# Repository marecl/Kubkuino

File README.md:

# Contactless liquid watchdog

Perfect for watching your coffee. Now you won't forget, that you've made one.

Directories:  
	* Dokumentacje - Documentation and final version of PC software  
	* Kubkuino - source code and case drawings  
	* Kubkuino_PC - PC software sources  
	* Obsolete - Old version  
	* RawDoc - Raw data for documentation  

ToDo list:  
	-Notification bar alarm,  
	-Print all COM ports on startup,   
	-Manual,  
	-Automatic config creation,
	-Migrate to V-USB?
  
Navigation:  
	1 click - enter menu/next item  
	Press and hold - Select/switch  
	
Arduino:  
  
	Source:  
		#define _NAME (String)"[NAME]" - Device default name  
		#define _PASS (String)"[4 digits]" - Set Bluetooth pairing PIN code  
		#define TONE [freq/tone] - Alarm frequency (or tone, based on vars.h)  
		#define ALARM_TIME [milliseconds] - Alarm duration  
  
	Bluetooth commands:  
		e; - Establish a connection (returns "HELLO\r\n") - must be sent!  
		qquit; - Disconnect - must be sent! 
		CXX.X; - Set 'cold' temperature  
		HXX.X; - Set 'hot' temperature  
		C?;/H?; - Check temperatures  
		r; - Current reading  
		S[AT command]; - Executes arbitary AT command, returns module's response  
		DXY; - Management:  
			0Y* - LCD  
			1Y* - Backlight  
			2Y* - Bluetooth  
			3Y* - LED  
			4Y* - Alarm mute  
			5 - Status of: LCD, Backlight, LED, Mute (4 bits)
			6 - Sleep mode  
			B - Revert bluetooth module to factory defaults  
			D - Device defaults  
			L - Load settings from EEPROM  
			S - Save settings to EEPROM  
  
		*(0 - OFF, 1 - ON, ? - Check status)

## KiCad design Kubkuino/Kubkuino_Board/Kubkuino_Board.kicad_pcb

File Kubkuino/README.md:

Parts:
* SSD1306 128x64 OLED display
* 3 LEDs - red, green and blue
* MLX90614 IR temperature sensor

Designed in KiCAD.  
Board has two layers, but the bottom one is only for ICSP header.  
All goldpin headers/sockets are SMD.

Drawings made in DraftSight. Unfortunately - you have to measure everything on your own.

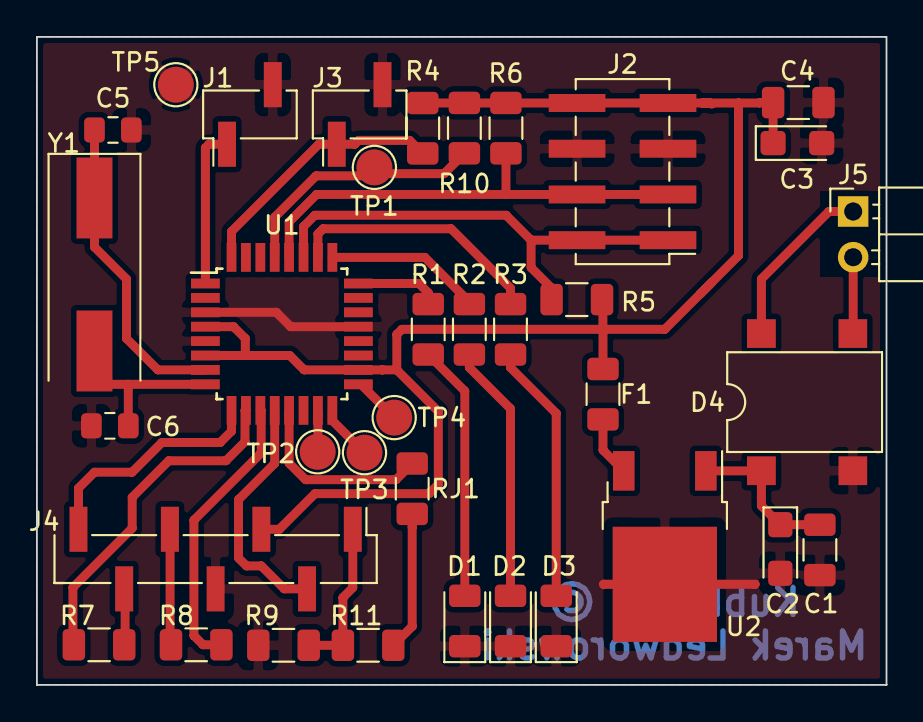
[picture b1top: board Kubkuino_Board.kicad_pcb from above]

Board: 2 copper layers, 47.2 x 36.0 mm, 36 parts (0 on the bottom side), 31 nets.

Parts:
C1, C4: 100nF; C_1206_3216Metric
C2, C3: 1uF; CP_EIA-3216-18_Kemet-A
C5, C6: 22pF; C_0805_2012Metric_Pad1.15x1.40mm_HandSolder
D1: LED_R; LED_1206_3216Metric
D2: LED_G; LED_1206_3216Metric
D3: LED_B; LED_1206_3216Metric
D4: DF08M; Diode_Bridge_DIP-4_W7.62mm_P5.08mm
F1: 500mA 6V; R_1206_3216Metric
J1: Piezo; PinHeader_1x02_P2.54mm_Vertical_SMD_Pin1Left
J2: I2C; PinHeader_2x04_P2.54mm_Vertical_SMD
J3: Button; PinHeader_1x02_P2.54mm_Vertical_SMD_Pin1Left
J4: Bluetooth; PinHeader_1x07_P2.54mm_Vertical_SMD_Pin1Left
J5: AC/DC In (12V); PinHeader_1x02_P2.54mm_Horizontal
R1, R2, R3: 220; R_1206_3216Metric
R4: 1k; R_1206_3216Metric
R5, R6, R7, R8, R11: 4k7; R_1206_3216Metric
R9, R10: 10k; R_1206_3216Metric
RJ1: 0; R_1206_3216Metric
TP1: RESET; TestPoint_Pad_D2.0mm
TP2: MOSI; TestPoint_Pad_D2.0mm
TP3: MISO; TestPoint_Pad_D2.0mm
TP4: SCK; TestPoint_Pad_D2.0mm
TP5: GND; TestPoint_Pad_D2.0mm
U1: ATmega328P-AU; TQFP-32_7x7mm_P0.8mm
U2: LM7805_TO220; TO-252-2
Y1: Crystal; Crystal_SMD_HC49-SD

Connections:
5V: C3.1, C4.1, F1.1, J2.7, J2.8, J4.3, R4.1, R5.2, R6.2, R10.1, U1.4, U1.6, U1.18
/MISO: TP3.1, U1.16
/MOSI: TP2.1, U1.15
/SCK: TP4.1, U1.17
BTen: J4.2, U1.12
BTkey: RJ1.1, U1.13
Brx: R7.2, U1.10
BtConn: J4.7, U1.9
Btx: R8.2, U1.11
Button: J3.1, R4.2, U1.32
GND: C1.2, C2.2, C3.2, C4.2, C5.2, C6.2, D1.1, D2.1, D3.1, D4.2, J1.2, J2.5, J2.6, J3.2, J4.4, R9.1, TP5.1, U1.3, U1.5, U1.21, U2.2
unnamed: C1.1, C2.1, D4.1, U2.1
unnamed: D1.2, R1.1
unnamed: D2.2, R2.1
unnamed: D3.2, R3.1
unnamed: D4.3, J5.2
unnamed: D4.4, J5.1
unnamed: F1.2, U2.3
unnamed: J1.1, U1.1
unnamed: J4.1, R9.2, R11.2
unnamed: J4.5, R8.1
unnamed: J4.6, R7.1
unnamed: R1.2, U1.24
unnamed: R2.2, U1.25
unnamed: R3.2, U1.26
unnamed: R11.1, RJ1.2
Reset: R10.2, TP1.1, U1.29
SCL: J2.3, J2.4, R6.1, U1.28
SDA: J2.1, J2.2, R5.1, U1.27
xtal1: C5.1, U1.7, Y1.1
xtal2: C6.1, U1.8, Y1.2

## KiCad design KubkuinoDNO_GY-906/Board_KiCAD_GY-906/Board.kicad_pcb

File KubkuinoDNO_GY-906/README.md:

# Specjalizowany czujnik temperaturowy:
## Mikroprocesorowy analizator cieplny

Zrobiłeś kawę albo herbatę i nie chcesz pilnować aż ostygnie? To coś dla Ciebie!
  
Do zrobienia:  
	-Ładniejszy interfejs,  
	-Naprawa wskaźników temperatury  
	-Rozróżnianie HELLO_STD od HELLO_IR (GY-906)  
	-Zmiana wyświetlacza na SSD1306 128x32 (i2c)  
	
Arduino:  
  
	Kod:  
		#define _NAME (String)"[NAZWA]" - Ustawia nazwę jako domyślną  
		#define _PASS (String)"[4 cyfry]" - Ustawia wpisane cyfry jako hasło do parowania  
		#define TONE [TON] - Dźwięk alarmu (uzupełnić na podstawie vars.h)  
		#define ALARM_TIME [milisekundy] - Ile milisekund Arduino ma piszczeć  
  
	Komendy:  
		X - Pierwszy argument  
		Y - Drugi argument  
  
		e; - Nawiązanie połączenia (zwraca "HELLO_IR\r\n") MUSI ZOSTAĆ WYSŁANE  
		qquit; - Rozłączenie MUSI ZOSTAĆ WYSŁANE (specjanie takie długie - na wypadek błędu komunikacji,  
			który wysyła 'q' zamiast 'r'. Nie wiem czemu.)  
		CXX.X; - Ustawienie temperatury zimna  
		HXX.X; - Ustawienie temperatury ciepła  
			C?;/H?; - sprawdzenie temperatur  
		S[komenda AT]; - Przesyła komendę AT do modułu Bluetooth. Zwraca odpowiedź modułu.  
		d; - Reset modułu Bluetooth, ustawienie domyślnej nazwy i hasła  
		r - Zwraca bieżący odczyt z czujnika  
		t; - Zwraca stan jako char (H - Hot, R - Ready, C - Cold)  
		DXY; - Moduł zarządzania komponentami:  
			0Y* - LCD (1 - włącz, 0 - wyłącz)  
			1Y* - Podswietlenie (1 - włącz, 0 - wyłącz)  
			2Y - BT (1 - włącz, 0 - wyłącz)  
			3Y* - LED (1 - włącz, 0 - wyłącz)  
			4Y* - Wyciszenie (1 - wyciszony, 0 - głośny)  
			6 - Status LCD, Podświetlenie, LED, Alarm (1 - włączony, 0 - wyłączony)  
			8 - Przejście w tryb uśpienia  
  
		*Jak jako argument poda się znak zapytania (?) zostanie zwrócony stan pojedynczego modułu  
  
Każda komenda jest zakończona średnikiem ';'!

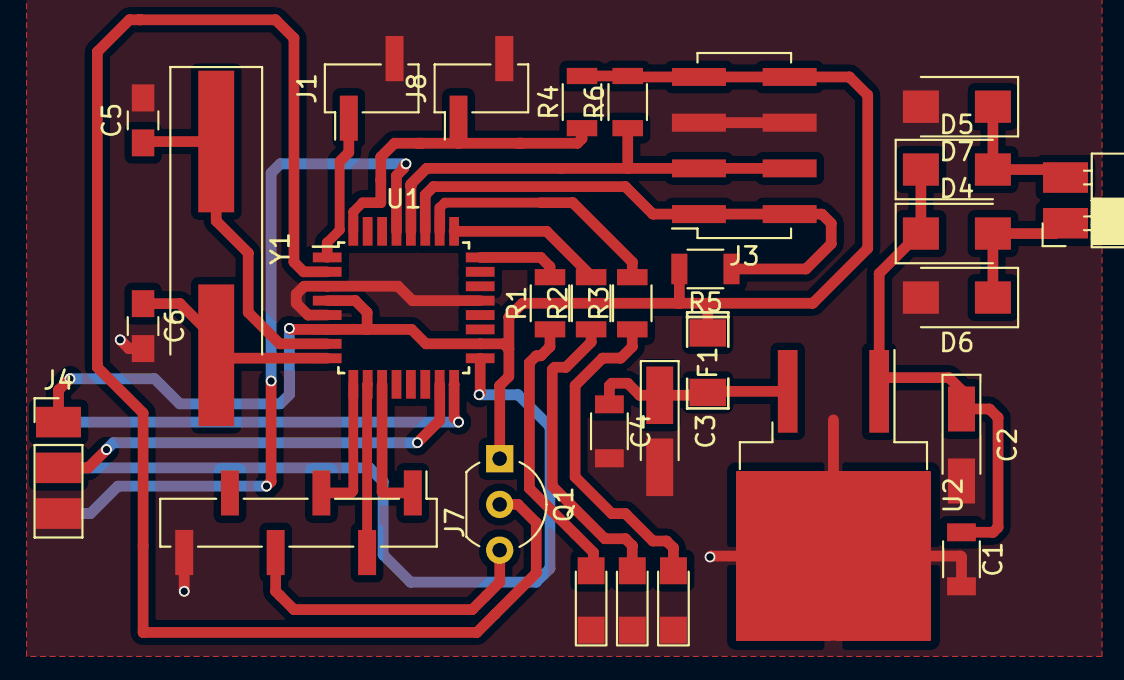
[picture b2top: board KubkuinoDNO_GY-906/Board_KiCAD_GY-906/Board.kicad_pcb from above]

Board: 2 copper layers, 31 parts (1 on the bottom side), 27 nets.

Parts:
C1, C4: 100nF; C_1206
C2, C3: 1uF; CP_Tantalum_Case-A_EIA-3216-18_Hand
C5, C6: 22pF; C_0805_HandSoldering
D1: LED_R; LED_1206
D2: LED_G; LED_1206
D3: LED_B; LED_1206
D4, D5, D6, D7: 1N4007; D_SMA
F1: 500mA 6V; SMD-1206_Pol
J1: Piezo; Pin_Header_Straight_1x02_Pitch2.54mm_SMD_Pin1Left
J2, J4: Conn_01x03; Socket_Strip_Straight_1x03_Pitch2.54mm
J3: I2C; Socket_Strip_Straight_2x04_Pitch2.54mm_SMD
J6: AC/DC In (12V); Socket_Strip_Angled_1x02_Pitch2.54mm
J7: Bluetooth; Pin_Header_Straight_1x06_Pitch2.54mm_SMD_Pin1Left
J8: Button; Pin_Header_Straight_1x02_Pitch2.54mm_SMD_Pin1Left
Q1: S8050; TO-92_Inline_Wide
R1, R2, R3: 220; R_1206
R4: 1k; R_1206
R5, R6: 4k7; R_1206
U1: ATMEGA328P-AU; TQFP-32_7x7mm_Pitch0.8mm
U2: LM7805_TO220; TO-263-2
Y1: Crystal; Crystal_SMD_HC49-SD_HandSoldering

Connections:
5V: F1.1, J3.7, J3.8, J4.1, Q1.1, R4.2, R5.2, R6.2, U1.4, U1.6, U1.18
BT: Q1.2, U1.2
Bkey: J7.1, U1.11
Brx: J7.2, U1.10
Btx: J7.3, U1.9
Button: J8.1, R4.1, U1.32
GND: C1.2, C2.2, C3.2, C4.2, C5.2, C6.2, D1.1, D2.1, D3.1, D6.2, D7.2, J1.2, J3.5, J3.6, J4.3, J7.6, J8.2, U1.3, U1.5, U1.21, U2.2
unnamed: C1.1, C2.1, D4.1, D5.1, U2.1
unnamed: C3.1, C4.1, F1.2, U2.3
unnamed: D1.2, R1.1
unnamed: D2.2, R2.1
unnamed: D3.2, R3.1
unnamed: D4.2, D6.1, J6.1
unnamed: D5.2, D7.1, J6.2
unnamed: J1.1, U1.1
unnamed: J2.1, U1.16
unnamed: J2.2, U1.17
unnamed: J4.2, U1.15
unnamed: J7.4, Q1.3
unnamed: R1.2, U1.24
unnamed: R2.2, U1.25
unnamed: R3.2, U1.26
Reset: J2.3, U1.29
SCL: J3.3, J3.4, R6.1, U1.28
SDA: J3.1, J3.2, R5.1, U1.27
xtal1: C5.1, U1.7, Y1.1
xtal2: C6.1, U1.8, Y1.2

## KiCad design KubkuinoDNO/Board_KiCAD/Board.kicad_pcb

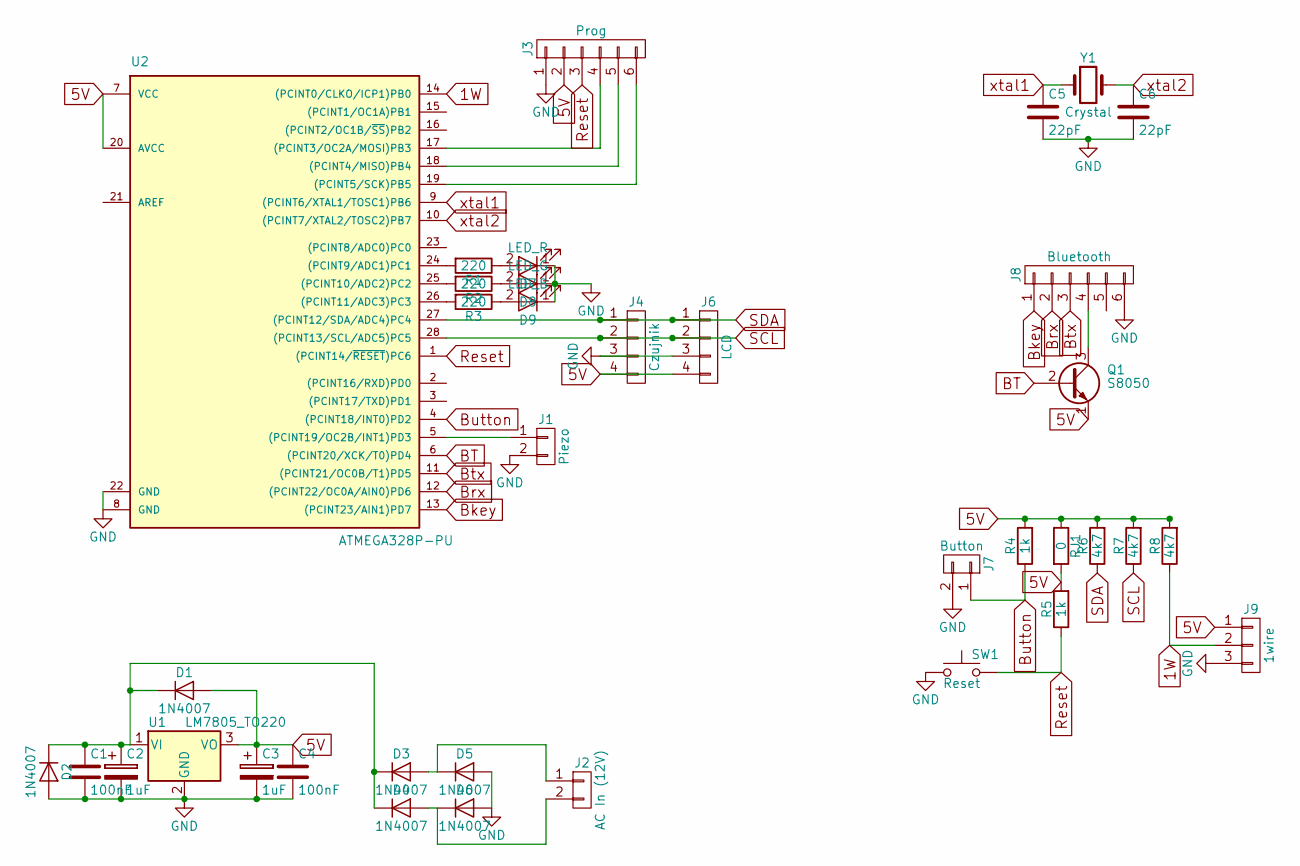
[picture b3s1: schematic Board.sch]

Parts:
C1, C4: 100nF; C_1206
C2, C3: 1uF; CP_Tantalum_Case-A_EIA-3216-18_Hand
C5, C6: 22pF; C_0805_HandSoldering
D1, D2, D3, D4, D5, D6: 1N4007; D_SMA
D7: LED_R; LED_1206
D8: LED_G; LED_1206
D9: LED_B; LED_1206
J1: Piezo; Pin_Header_Straight_1x02_Pitch2.54mm_SMD_Pin1Left
J2: AC In (12V); Pin_Header_Straight_1x02_Pitch2.54mm_SMD_Pin1Left
J3: Prog; Pin_Header_Straight_1x06_Pitch2.54mm_SMD_Pin1Left
J4: Czujnik; Pin_Header_Straight_1x04_Pitch2.54mm_SMD_Pin1Left
J6: LCD; Pin_Header_Straight_1x04_Pitch2.54mm_SMD_Pin1Left
J7: Button; Pin_Header_Straight_1x02_Pitch2.54mm_SMD_Pin1Left
J8: Bluetooth; Pin_Header_Straight_1x06_Pitch2.54mm_SMD_Pin1Left
J9: 1wire; Pin_Header_Straight_1x03_Pitch2.54mm_SMD_Pin1Left
Q1: S8050; TO-92_Inline_Wide
R1, R2, R3: 220; R_1206
R4, R5: 1k; R_1206
R6, R7, R8: 4k7; R_1206
RJ1: 0
SW1: Reset; SW_SPST_B3SL-1002P
U1: LM7805_TO220; TO-263-2
U2: ATMEGA328P-PU; TQFP-32_7x7mm_Pitch0.8mm
Y1: Crystal; Crystal_SMD_HC49-SD

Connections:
1W: J9.2, R8.1, U2.14 ((PCINT0/CLKO/ICP1)PB0)
5V: C3.1, C4.1, D1.2 (A), J3.2, J4.4, J6.4, J9.1, Q1.1 (E), R4.2, R5.2, R6.2, R7.2, R8.2, RJ1.1, RJ1.2, U1.3 (VO), U2.7 (VCC), U2.20 (AVCC)
BT: Q1.2 (B), U2.6 ((PCINT20/XCK/T0)PD4)
Bkey: J8.1, U2.13 ((PCINT23/AIN1)PD7)
Brx: J8.2, U2.12 ((PCINT22/OC0A/AIN0)PD6)
Btx: J8.3, U2.11 ((PCINT21/OC0B/T1)PD5)
Button: J7.1, R4.1, U2.4 ((PCINT18/INT0)PD2)
GND: C1.2, C2.2, C3.2, C4.2, C5.2, C6.2, D2.2 (A), D5.2 (A), D6.2 (A), D7.1 (K), D8.1 (K), D9.1 (K), J1.2, J3.1, J4.3, J6.3, J7.2, J8.6, J9.3, SW1.1, U1.2 (GND), U2.8 (GND), U2.22 (GND)
unnamed: C1.1, C2.1, D1.1 (K), D2.1 (K), D3.1 (K), D4.1 (K), U1.1 (VI)
unnamed: D3.2 (A), D5.1 (K), J2.1
unnamed: D4.2 (A), D6.1 (K), J2.2
unnamed: D7.2 (A), R1.1
unnamed: D8.2 (A), R2.1
unnamed: D9.2 (A), R3.1
unnamed: J1.1, U2.5 ((PCINT19/OC2B/INT1)PD3)
unnamed: J3.4, U2.17 ((PCINT3/OC2A/MOSI)PB3)
unnamed: J3.5, U2.18 ((PCINT4/MISO)PB4)
unnamed: J3.6, U2.19 ((PCINT5/SCK)PB5)
unnamed: J8.4, Q1.3 (C)
unnamed: R1.2, U2.24 ((PCINT9/ADC1)PC1)
unnamed: R2.2, U2.25 ((PCINT10/ADC2)PC2)
unnamed: R3.2, U2.26 ((PCINT11/ADC3)PC3)
Reset: J3.3, R5.1, SW1.2, U2.1 ((PCINT14/~RESET~)PC6)
SCL: J4.2, J6.2, R7.1, U2.28 ((PCINT13/SCL/ADC5)PC5)
SDA: J4.1, J6.1, R6.1, U2.27 ((PCINT12/SDA/ADC4)PC4)
xtal1: C5.1, U2.9 ((PCINT6/XTAL1/TOSC1)PB6), Y1.1
xtal2: C6.1, U2.10 ((PCINT7/XTAL2/TOSC2)PB7), Y1.2

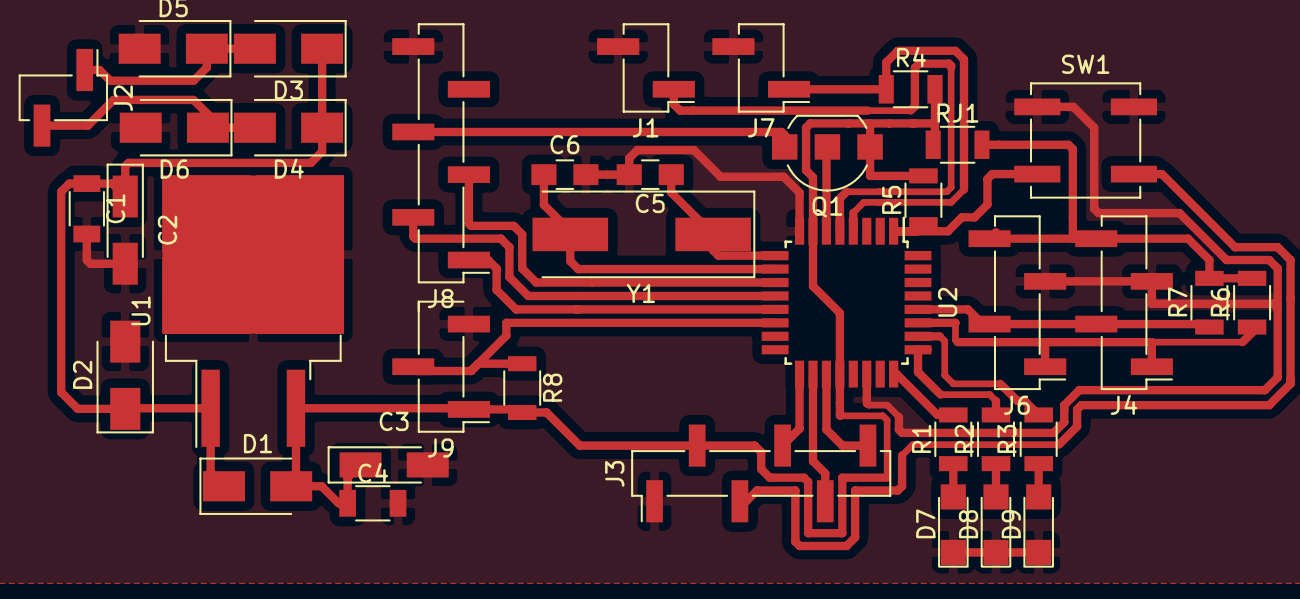
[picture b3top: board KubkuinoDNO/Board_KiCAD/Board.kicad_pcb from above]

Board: 2 copper layers, 37 parts (0 on the bottom side), 27 nets.

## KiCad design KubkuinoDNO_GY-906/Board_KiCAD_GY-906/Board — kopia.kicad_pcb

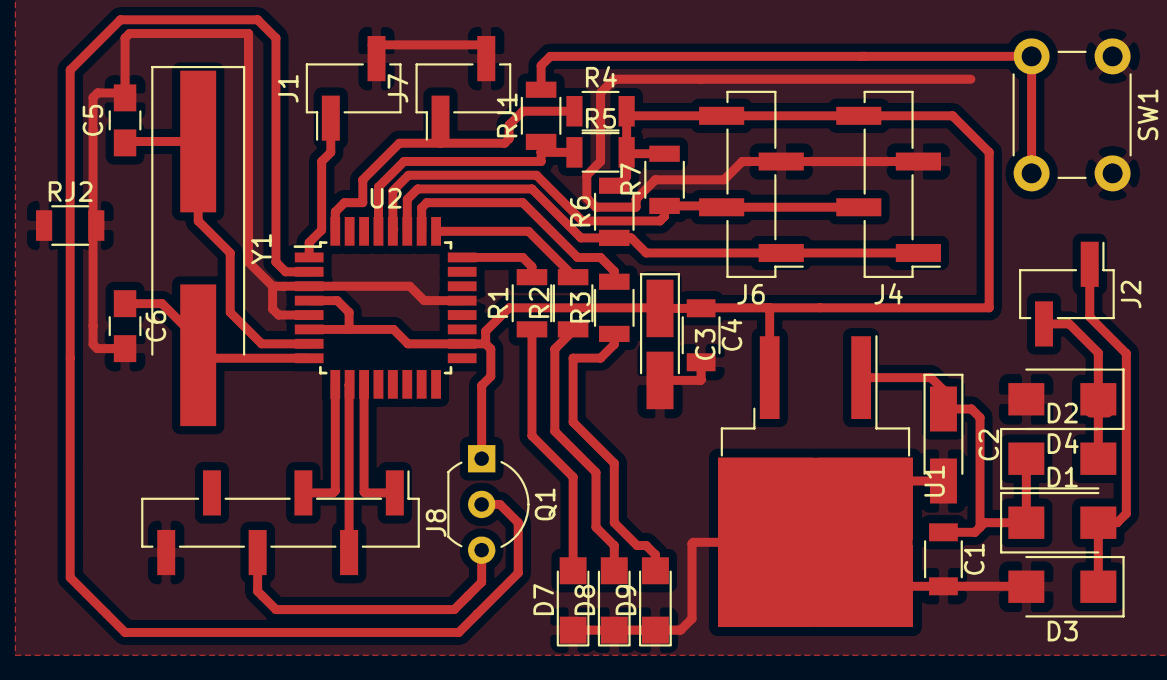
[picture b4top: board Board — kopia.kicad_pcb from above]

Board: 2 copper layers, 33 parts (0 on the bottom side), 24 nets.

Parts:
C1, C4: 100nF; C_1206
C2, C3: 1uF; CP_Tantalum_Case-A_EIA-3216-18_Hand
C5, C6: 22pF; C_0805_HandSoldering
D1, D2, D3, D4: 1N4007; D_SMA
D7: LED_R; LED_1206
D8: LED_G; LED_1206
D9: LED_B; LED_1206
J1: Piezo; Pin_Header_Straight_1x02_Pitch2.54mm_SMD_Pin1Left
J2: AC/DC In (12V); Pin_Header_Straight_1x02_Pitch2.54mm_SMD_Pin1Left
J4: Czujnik; Pin_Header_Straight_1x04_Pitch2.54mm_SMD_Pin1Left
J6: LCD; Pin_Header_Straight_1x04_Pitch2.54mm_SMD_Pin1Left
J7: Button; Pin_Header_Straight_1x02_Pitch2.54mm_SMD_Pin1Left
J8: Bluetooth; Pin_Header_Straight_1x06_Pitch2.54mm_SMD_Pin1Left
Q1: S8050; TO-92_Inline_Wide
R1, R2, R3: 220; R_1206
R4, R5: 1k; R_1206
R6, R7: 4k7; R_1206
RJ1, RJ2: 0; R_1206
SW1: Reset; SW_PUSH_6mm_h5mm
U1: LM7805_TO220; TO-263-2
U2: ATMEGA328P-AU; TQFP-32_7x7mm_Pitch0.8mm
Y1: Crystal; Crystal_SMD_HC49-SD_HandSoldering

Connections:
5V: C3.1, C4.1, J4.4, J6.4, Q1.1, R4.2, R5.2, R6.2, R7.2, U1.3, U2.4, U2.6, U2.18
BT: Q1.2, U2.2
Bkey: J8.1, U2.11
Brx: J8.2, U2.10
Btx: J8.3, U2.9
Button: J7.1, R4.1, U2.32
GND: C1.2, C2.2, C3.2, C4.2, C5.2, C6.2, D3.2, D4.2, D7.1, D8.1, D9.1, J1.2, J4.3, J6.3, J7.2, J8.6, RJ2.1, RJ2.2, SW1.1, U1.2, U2.3, U2.5, U2.21
unnamed: C1.1, C2.1, D1.1, D2.1, U1.1
unnamed: D1.2, D3.1, J2.1
unnamed: D2.2, D4.1, J2.2
unnamed: D7.2, R1.1
unnamed: D8.2, R2.1
unnamed: D9.2, R3.1
unnamed: J1.1, U2.1
unnamed: J8.4, Q1.3
unnamed: R1.2, U2.24
unnamed: R2.2, U2.25
unnamed: R3.2, U2.26
unnamed: RJ1.2, SW1.2
Reset: R5.1, RJ1.1, U2.29
SCL: J4.2, J6.2, R7.1, U2.28
SDA: J4.1, J6.1, R6.1, U2.27
xtal1: C5.1, U2.7, Y1.1
xtal2: C6.1, U2.8, Y1.2

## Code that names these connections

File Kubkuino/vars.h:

#define ctl 2 //Przycisk
#define buzz 3 //Buzzer
#define btconn 5 //BT connected
#define brx 6 //Bluetooth RX
#define btx 7 //Bluetooth TX
#define btpow 8 //Zasilanie BT
#define btkey 9 //BT Key
#define rled A1
#define gled A2
#define bled A3
#if F_CPU != 16000000
#undef F_CPU
#define F_CPU 16000000
#endif
#if (SSD1306_LCDHEIGHT != 64)
#error("Height incorrect, please fix Adafruit_SSD1306.h!");
#endif

/* Pomiary */
int8_t hot, cold;
double pomiar = 0, poppomiar = 0;

/* Alarm */
uint8_t alarmState = 0b000;
bool glosny, alarm = false;
uint32_t alarmStart = 0;

/* Zasilanie */
bool lcdon, dimlcd, ledon;

PROGMEM const uint8_t icon[] = { //Bluetooth
  0b00000011, 0b00000000,
  0b00000011, 0b11000000,
  0b00000011, 0b11000000,
  0b00110011, 0b00110000,
  0b00110011, 0b00001100,
  0b00001111, 0b00001100,
  0b00001111, 0b00110000,
  0b00000011, 0b11000000,
  0b00000011, 0b11000000,
  0b00001111, 0b00110000,
  0b00001111, 0b00001100,
  0b00110011, 0b00001100,
  0b00110011, 0b00110000,
  0b00000011, 0b11000000,
  0b00000011, 0b11000000,
  0b00000011, 0b00000000
};

PROGMEM const uint8_t state_hot[] = {
  0b00000110, 0b00000110, 0b01111000,
  0b00000110, 0b00000110, 0b01111000,
  0b00011110, 0b01111000, 0b00011000,
  0b00011110, 0b01111000, 0b00011000,
  0b01111000, 0b00011000, 0b01111000,
  0b01111000, 0b00011000, 0b01111000,
  0b01111000, 0b00011000, 0b01100000,
  0b01111000, 0b00011000, 0b01100000,
  0b00011110, 0b00000000, 0b01100000,
  0b00011110, 0b00000000, 0b01100000,
  0b00011110, 0b00011110, 0b01111000,
  0b00011110, 0b00011110, 0b01111000,
  0b01111000, 0b01111000, 0b00011110,
  0b01111000, 0b01111000, 0b00011110,
  0b00000000, 0b00011000, 0b00000000,
  0b00000000, 0b00011000, 0b00000000,
};

PROGMEM const uint8_t state_ready[] = {
  0b00000000, 0b00000000, 0b00110000,
  0b00000000, 0b00000000, 0b00110000,
  0b00000000, 0b00000000, 0b11111100,
  0b00000000, 0b00000000, 0b11111100,
  0b00000000, 0b00000011, 0b11110000,
  0b00000000, 0b00000011, 0b11110000,
  0b00000000, 0b00001111, 0b11000000,
  0b00000000, 0b00001111, 0b11000000,
  0b00001100, 0b00111111, 0b00000000,
  0b00001100, 0b00111111, 0b00000000,
  0b00111111, 0b11111100, 0b00000000,
  0b00111111, 0b11111100, 0b00000000,
  0b00001111, 0b11110000, 0b00000000,
  0b00001111, 0b11110000, 0b00000000,
  0b00000011, 0b11000000, 0b00000000,
  0b00000011, 0b11000000, 0b00000000,
};

PROGMEM const uint8_t state_cold[] = {
  0b00000000, 0b00000000, 0b00000000,
  0b00000000, 0b00000000, 0b00000000,
  0b00000111, 0b10000001, 0b11100000,
  0b00000111, 0b10000001, 0b11100000,
  0b00000111, 0b10000001, 0b11100000,
  0b00000111, 0b10000001, 0b11100000,
  0b00000000, 0b00000000, 0b00000000,
  0b00000000, 0b00000000, 0b00000000,
  0b00000001, 0b11111111, 0b10000000,
  0b00000001, 0b11111111, 0b10000000,
  0b00000111, 0b11111111, 0b11100000,
  0b00000111, 0b11111111, 0b11100000,
  0b00000111, 0b10000001, 0b11100000,
  0b00000111, 0b10000001, 0b11100000,
  0b00000000, 0b00000000, 0b00000000,
  0b00000000, 0b00000000, 0b00000000,
};

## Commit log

2017-04-03 :lollipop: Added .gitattributes & .gitignore files
2017-04-03 Cleanup
2017-04-03 Ostatnie szlify
2017-04-04 Updates
    Dodany quickstart dla programu. Jeszcze pare zabiegow kosmetycznych i
    bedzie git
2017-04-04 Little fixes
2017-04-04 Koniec na dzisiaj
2017-04-05 Instrukcje, szlify
    Dodałem strzałki przy wyborze trybu pomiaru, instrukcję urządzenia i
    kilka zdjęć
2017-04-05 na szybko żeby nie stracić
    do zrobienia dokumentacja ostateczna
2017-04-05 Moze juz koniec
2017-04-05 Poprawki
2017-06-26 Started working on Serial version
    TODO:
    Update everything from main version
    Prepare board in KiCAD instead of Fritzing
    Get IR contactless temperature sensor and begin working with it
    I've probably screwed up PC application, so... yeah. VC++Express is not
    so well copmpatible with 2017...
2017-07-23 Updates
    Updated to VS2017 (Community)
    Optimized main sketch (no compiler warnings)
    Made new full-smd board in KiCAD
2017-07-27 Upgrades
    Aktualizacja głównego kodu do użycia czujnika podczerwonego
    Ukończenie płytki (SMD)
2017-09-08 Fixed SMD board
2017-09-20 Finished PCB
2017-10-12 Minor optimization
    Board GY906:
    Removed ICSP header and replaced with pads
    Moved power input to the edge
    Added fuse after LM7805
    GY906 sketch:
    Alarm has got new launch method (removed booleans)
2018-03-09 Large update
    Removed old hardware version
    Custom case to laser-print (plexi, plywood 3mm)
    Infrared sensor
    Bluetooth connectivity
    Local settings saving
    Better PC application
2019-04-30 Large update
    Code:
    Changed name of file
    Added translations (PL/ENG)
    Removed unneeded libraries
    Board:
    Upgraded schematic with KiCAD 5.1.2
2019-05-23 Board optimization
    Smaller board (couple of millimeters shorter)
    Removed ICSP header
    Added pads for programming
    Changed rectifying section: DF08S (in schematic: DF08M, for THT change pads to through-hole)
    Added missing resistor on reset line
    No connections from before the fuse
